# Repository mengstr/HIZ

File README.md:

# Human Infected Zombie

An entry to the [Square Inch Project](https://hackaday.io/project/7813) contest on Hackaday.io

## Hardware
The board is a small (25 mm square) PCB with an IR transmitter and receiver for communications with other players and three colored LEDs that indicate the current state of the player.

The board is powered by a CR2032 coin cell mounted at the back of the PCB and it will hopefully last long enough for a full day of playing.

There's also an on/off slider switch and a tactile button for configuration changes on the PCB.

The game is running on a PIC12LF???? having 1.5K flash and 64 bytes of RAM.

## Gameplay 
#### States
A player can be in three different states:

1. Human - Green LED
2. Infected - Yellow LED
3. Zombie - Red LED

#### State changes

* A *Zombie* will turn a *Human* into an *Infected*
* A (multiple?) *Human* will heal an *Infected* into a *Human* again.
* An *Infected* will after some time automatically become a *Zombie*
* A *Zombie* could possibly be treated into a *Human* or *Infected* by visiting (multiple?) *Hospital* (fixed locations with transmit-ony boards)

## IR Protocol
In order to prevent cheating (or at least make it harder) there should be a two-way communications between the nodes in order for a state change to take place. Or else one can simply avoid getting infected by just covering the IR receiver.

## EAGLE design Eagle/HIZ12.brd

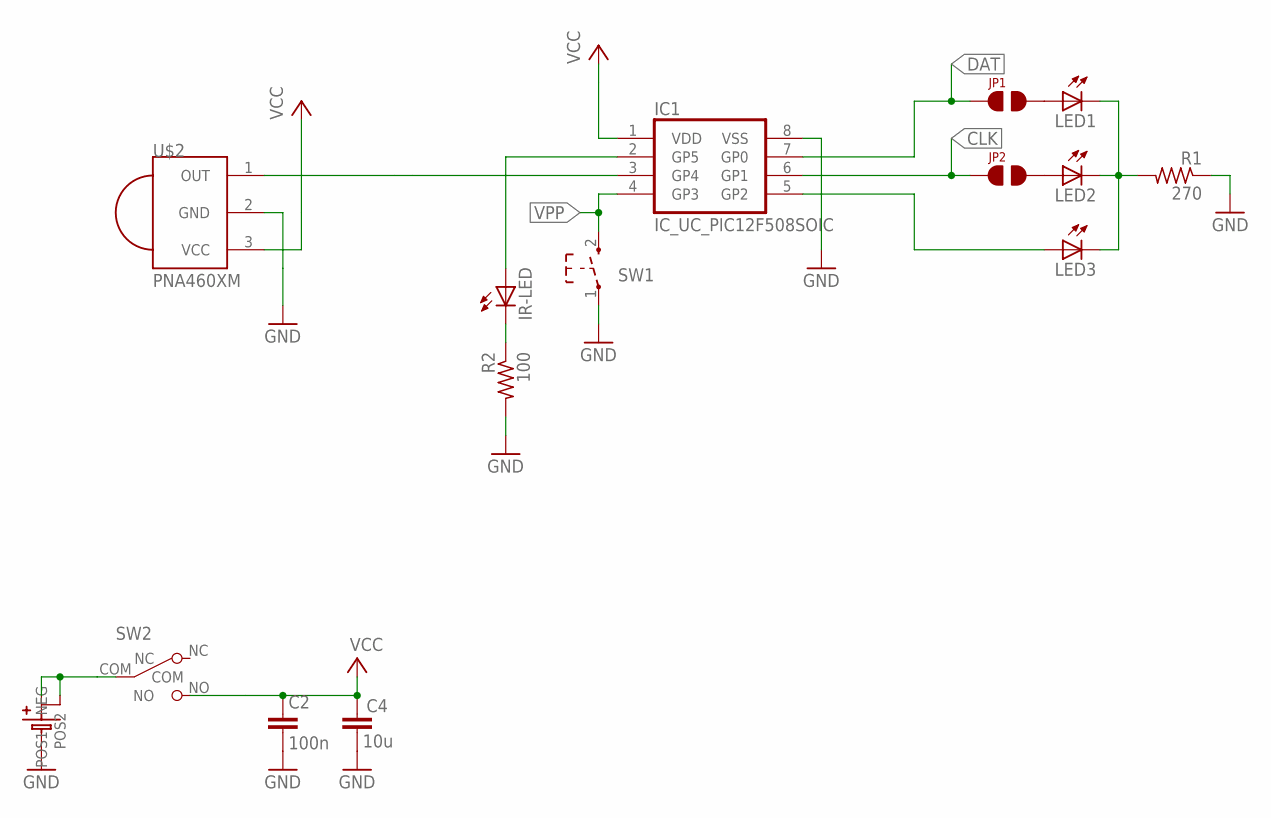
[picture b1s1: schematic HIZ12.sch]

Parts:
C2: 100n; C805
C4: 10u; C805
IC1: IC_UC_PIC12F508SOIC; SO-8
IR-LED: LEDSMT1206; 1206
JP1, JP2: JP2-TINY; JP2-T
LED1, LED2, LED3: LED-0805; LED-805
R1: 270; R0805
R2: 100; R0805
SW1: SW_TACT_2P-3X6; SW_TACT_3X6
SW2: SW_SLIDE; SLIDE_SWITCH_SMD
U$2: PNA460XM
U$3: BATTERYCOIN-12MM-SMD; CR1220-SMD

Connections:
CLK: IC1.6 (GP1), JP2.P$1
DAT: IC1.7 (GP0), JP1.P$1
GND: C2.2, C4.2, IC1.8 (VSS), R1.1, R2.2, SW1.1, U$2.2 (GND), U$3.- (NEG)
unnamed: LED1.C, LED2.C, LED3.C, R1.2
unnamed: JP1.P$2, LED1.A
unnamed: JP2.P$2, LED2.A
unnamed: IC1.5 (GP2), LED3.A
unnamed: SW2.COM, U$3.+$1 (POS1), U$3.+$2 (POS2)
unnamed: IC1.3 (GP4), U$2.1 (OUT)
unnamed: IR-LED.C, R2.1
unnamed: IC1.2 (GP5), IR-LED.A
VCC: C2.1, C4.1, IC1.1 (VDD), SW2.NO, U$2.3 (VCC)
VPP: IC1.4 (GP3), SW1.2 (3)

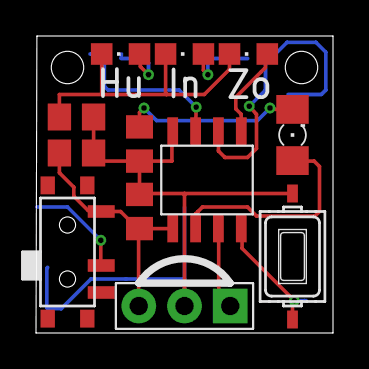
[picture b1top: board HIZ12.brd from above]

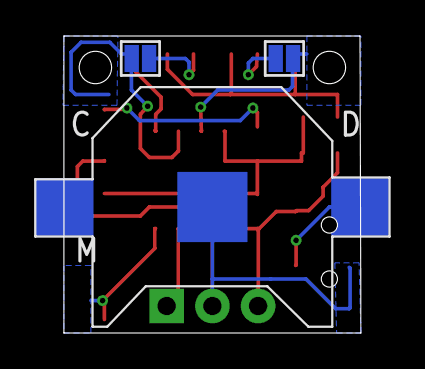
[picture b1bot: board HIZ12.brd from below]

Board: 2 copper layers, 16.5 x 16.5 mm, 15 parts (3 on the bottom side), 13 nets.

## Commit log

2015-10-01 Added PCB render to readme
2015-10-01 Added Frame to schematics
2015-10-01 Updated info in Frame, added part values.
2015-10-02 Added version with CR1220 battery

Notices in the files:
parts and their libraries:
SmallRoomLabs_Misc: Copyright(c) Mats Engstrom - mats@smallroomlabs.com
SmallRoomLabs_Misc: Creative Commons Attribution-ShareAlike 4.0 (CC BY-SA 4.0)
